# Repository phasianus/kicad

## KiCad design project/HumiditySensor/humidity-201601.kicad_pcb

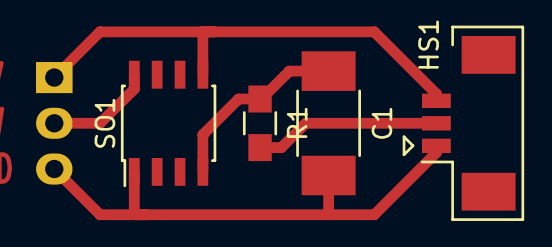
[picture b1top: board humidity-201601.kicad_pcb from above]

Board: 2 copper layers, 5 parts (1 on the bottom side), 5 nets.

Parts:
C1: 0.01uF; C_1812_HandSoldering
HS1: hih-5030-001; Connector_Molex_PicoBlade_53261-0371
P1: CONN_01X03; Pin_Header_Straight_1x03
R1: 100k; R_0805_HandSoldering
SO1: ds2438; SOIC-8_3.9x4.9mm_Pitch1.27mm

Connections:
unnamed: C1.1, R1.1, SO1.4
unnamed: C1.2, HS1.1, P1.3, SO1.1
unnamed: HS1.2, R1.2
unnamed: HS1.3, P1.1, SO1.5
unnamed: P1.2, SO1.8

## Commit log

2017-11-19 Init repository
2017-11-19 Import library
2017-11-19 Adding humiditiy sensor
